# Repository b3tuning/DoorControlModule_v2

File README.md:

# DoorControlModule_v2
Door Control Module v2.0 for Studebaker project.  

Utilizing an Arduino Nano for I/O

Pololu G2 High-Power Motor Driver 18v25 for control of window motor

Infineon Technologies TLE94108 8 channel Half Bridge driver for control of power folding mirrors

Door control module used in both Driver and Passenger doors.  Door control modules talk to eachother over arduino TX/RX lines.

Driver door module takes input via a Porsche window switch.  Door control module controls local window and mirror.  Communicates to passenger door control module to control passenger window and mirror.

Passenger door control module takes input via a porsche window switch.  Controls passenger window and mirror via commands sent from driver control module, or controls window via local window switch.  Sends button illumination command to driver control module.

Communication between Arduino and TLE94108 is via SPI.

TODO: organize README.md file 

TODO: finish TLE94108 library and implement SPI and update code to use library

TODO: commit current code base

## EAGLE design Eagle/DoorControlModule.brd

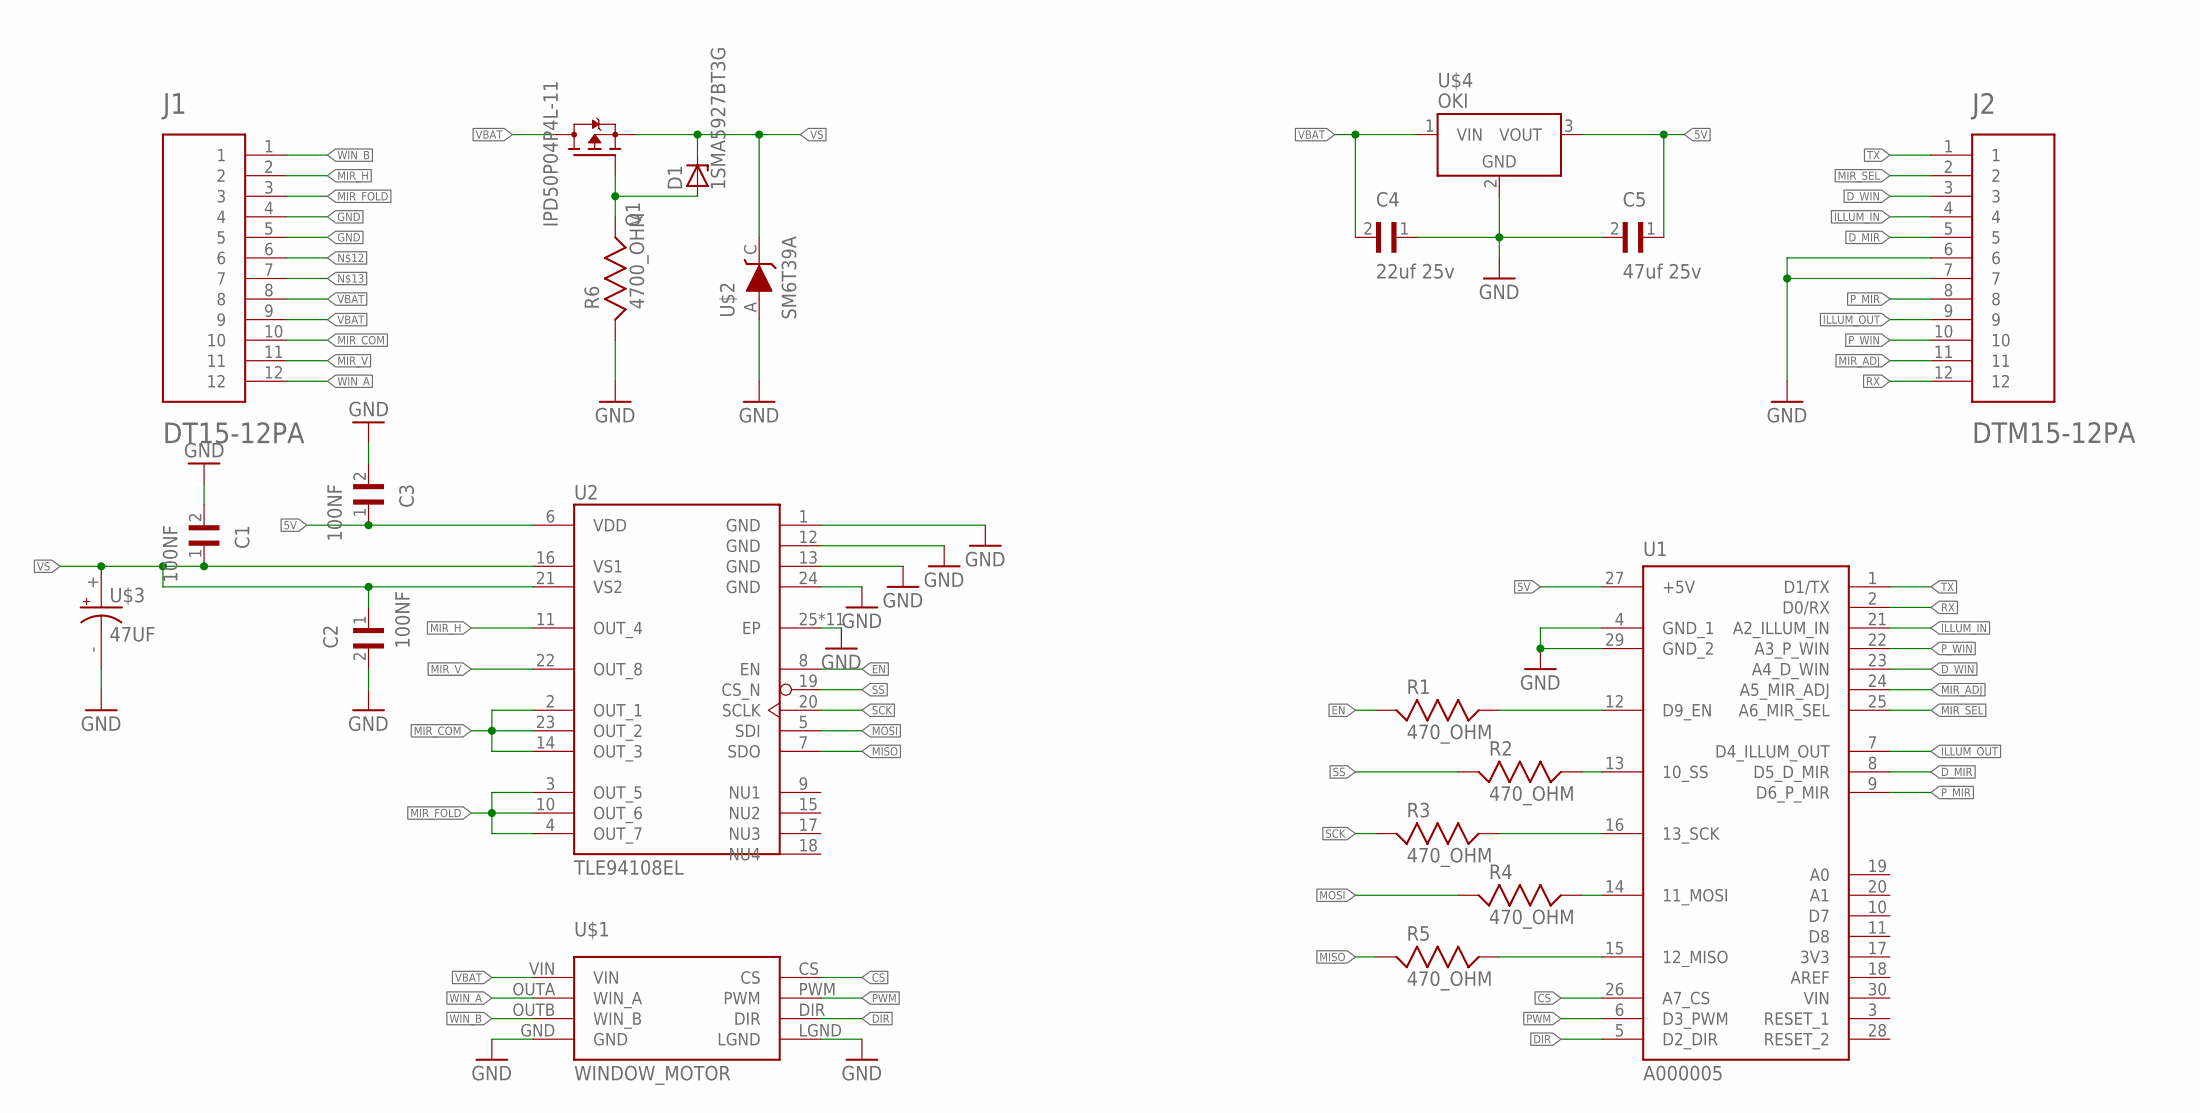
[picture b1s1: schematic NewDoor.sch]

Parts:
C1, C2, C3: 100NF; CAPC3216X110N
C4: 22uf 25v; CAP3216X125N
C5: 47uf 25v; CAP3216X125N
D1: 1SMA5927BT3G; DO214AC
J1: DT15-12PA; TE_DT15-12PA
J2: DTM15-12PA; TE_DTM15-12PA
Q1: IPD50P04P4L-11; DPAK228P998X235-3N
R1, R2, R3, R4, R5: 470_OHM; RESC3216X65
R6: 4700_OHM; RESC3216X70
U1: A000005; ARDUINO_A000005
U2: TLE94108EL; SOP65P600X170-25N
U$1: WINDOW_MOTOR; POLOLU
U$2: SM6T39A
U$3: 47UF; CAPAE1030X1200
U$4: OKI; OKI-78SR-H

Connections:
5V: C3.1, C5.1, U1.27 (+5V), U2.6 (VDD), U$4.3 (VOUT)
CS: U1.26 (A7_CS), U$1.CS
DIR: U1.5 (D2_DIR), U$1.DIR
D_MIR: J2.5, U1.8 (D5_D_MIR)
D_WIN: J2.3, U1.23 (A4_D_WIN)
EN: R1.1, U2.8 (EN)
EN_A: R1.2, U1.12 (D9_EN)
GATE: D1.A, Q1.1 (G), R6.2
GND: C1.2, C2.2, C3.2, C4.1, C5.2, J1.4, J1.5, J2.6, J2.7, R6.1, U1.4 (GND_1), U1.29 (GND_2), U2.1 (GND), U2.12 (GND), U2.13 (GND), U2.24 (GND), U2.25 (EP), U2.GND (EP), U2.GND1 (EP), U2.GND2 (EP), U2.GND3 (EP), U2.GND4 (EP), U2.GND5 (EP), U2.GND6 (EP), U2.GND7 (EP), U2.GND8 (EP), U2.GND9 (EP), U$1.GND, U$1.LGND, U$2.A, U$3.-, U$4.2 (GND)
ILLUM_IN: J2.4, U1.21 (A2_ILLUM_IN)
ILLUM_OUT: J2.9, U1.7 (D4_ILLUM_OUT)
MIR_ADJ: J2.11, U1.24 (A5_MIR_ADJ)
MIR_COM: J1.10, U2.2 (OUT_1), U2.14 (OUT_3), U2.23 (OUT_2)
MIR_FOLD: J1.3, U2.3 (OUT_5), U2.4 (OUT_7), U2.10 (OUT_6)
MIR_H: J1.2, U2.11 (OUT_4)
MIR_SEL: J2.2, U1.25 (A6_MIR_SEL)
MIR_V: J1.11, U2.22 (OUT_8)
MISO: R5.1, U2.7 (SDO)
MISO_A: R5.2, U1.15 (12_MISO)
MOSI: R4.1, U2.5 (SDI)
MOSI_A: R4.2, U1.14 (11_MOSI)
PWM: U1.6 (D3_PWM), U$1.PWM
P_MIR: J2.8, U1.9 (D6_P_MIR)
P_WIN: J2.10, U1.22 (A3_P_WIN)
RX: J2.12, U1.2 (D0/RX)
SCK: R3.1, U2.20 (SCLK)
SCK_A: R3.2, U1.16 (13_SCK)
SS: R2.1, U2.19 (CS_N)
SS_A: R2.2, U1.13 (10_SS)
TX: J2.1, U1.1 (D1/TX)
VBAT: C4.2, J1.8, J1.9, Q1.2 (D), U$1.VIN, U$4.1 (VIN)
VS: C1.1, C2.1, D1.C, Q1.3 (S), U2.16 (VS1), U2.21 (VS2), U$2.C, U$3.+
WIN_A: J1.12, U$1.OUTA (WIN_A)
WIN_B: J1.1, U$1.OUTB (WIN_B)

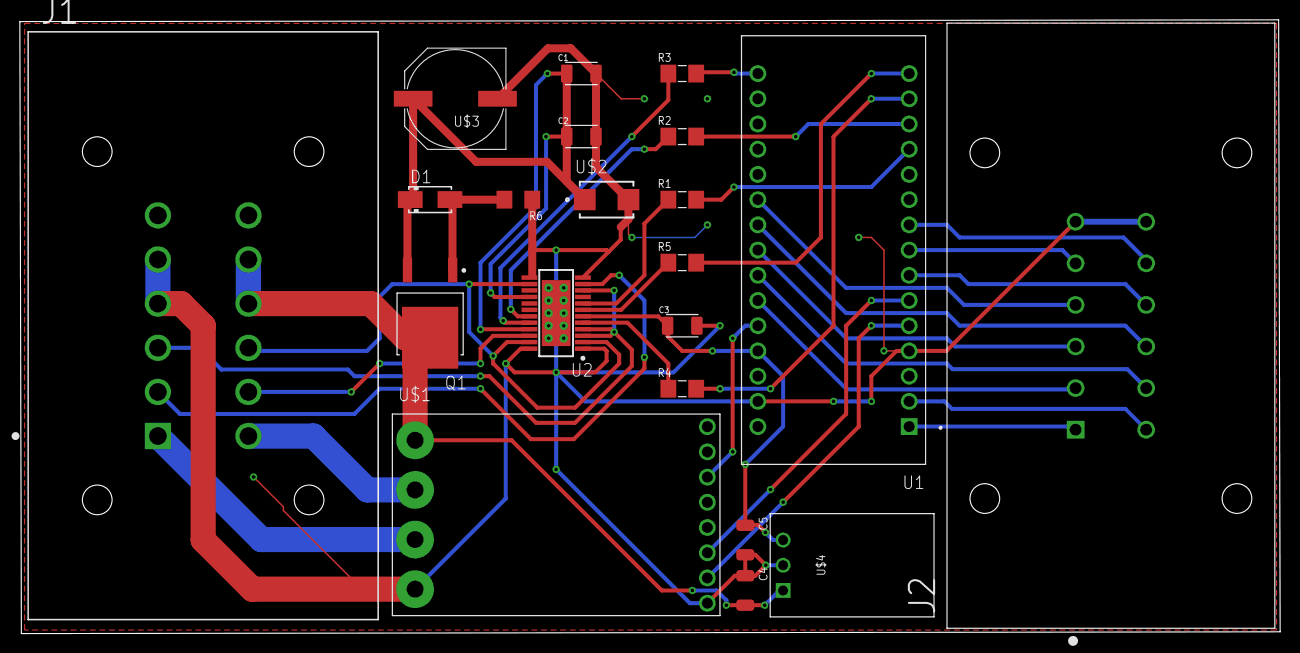
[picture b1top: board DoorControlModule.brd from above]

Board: 2 copper layers, 127.0 x 61.8 mm, 21 parts (0 on the bottom side), 34 nets.

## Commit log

2019-05-27 Add files via upload
    Added Eagle files and gerber files for Door Control Module
2019-05-27 Rename NewDoor.brd to Eagle/DoorControlModule.brd
2019-05-27 Rename NewDoor.sch to Eagle/DoorControlModule.sch
2019-05-27 Rename copper_bottom.gbr to CamOutput/Gerber/copper_bottom.gbr
2019-05-27 Rename drills.xln to CamOutput/Drill/drills.xln
2019-05-27 Rename copper_top.gbr to CamOutput/Gerber/copper_top.gbr
2019-05-27 Rename gerber_job.gbrjob to CamOutput/Gerber/gerber_job.gbrjob
2019-05-27 Rename profile.gbr to CamOutput/Gerber/profile.gbr
2019-05-27 Rename silkscreen_bottom.gbr to CamOutput/Gerber/silkscreen_bottom.gbr
2019-05-27 Rename silkscreen_top.gbr to CamOutput/Gerber/silkscreen_top.gbr
2019-05-27 Rename soldermask_bottom.gbr to CamOutput/Gerber/soldermask_bottom.gbr
2019-05-27 Rename soldermask_top.gbr to CamOutput/Gerber/soldermask_top.gbr
2019-05-27 Rename solderpaste_bottom.gbr to CamOutput/Gerber/solderpaste_bottom.gbr
2019-05-27 Rename solderpaste_top.gbr to CamOutput/Gerber/solderpaste_top.gbr
2019-05-27 Rename structure.hash to .pioenvs/structure.hash
